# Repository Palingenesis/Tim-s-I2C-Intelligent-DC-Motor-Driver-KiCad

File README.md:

# Tim-s-I2C-Intelligent-DC-Motor-Driver-KiCad<br>
<br>
This is my Intelligent I2C DC Motor Driver<br>
It is an STM8S103F3P6 cofigured as an I2C Slave to control a DC Motor using a H Bridge.<br>
It can recives signals from Quadratic Encoder to determin direction and position.<br>
Also with a Quadratic Encoder attached you can set soft limits.<br>
There are pinouts to add hard stops<br>
There is a pinout to add a Station to set a known position<br>
Details: https://www.hackster.io/Tim_Palingenesis/tim-s-i2c-intelligent-dc-motor-driver-82cda1

<picture>
  
</picture>

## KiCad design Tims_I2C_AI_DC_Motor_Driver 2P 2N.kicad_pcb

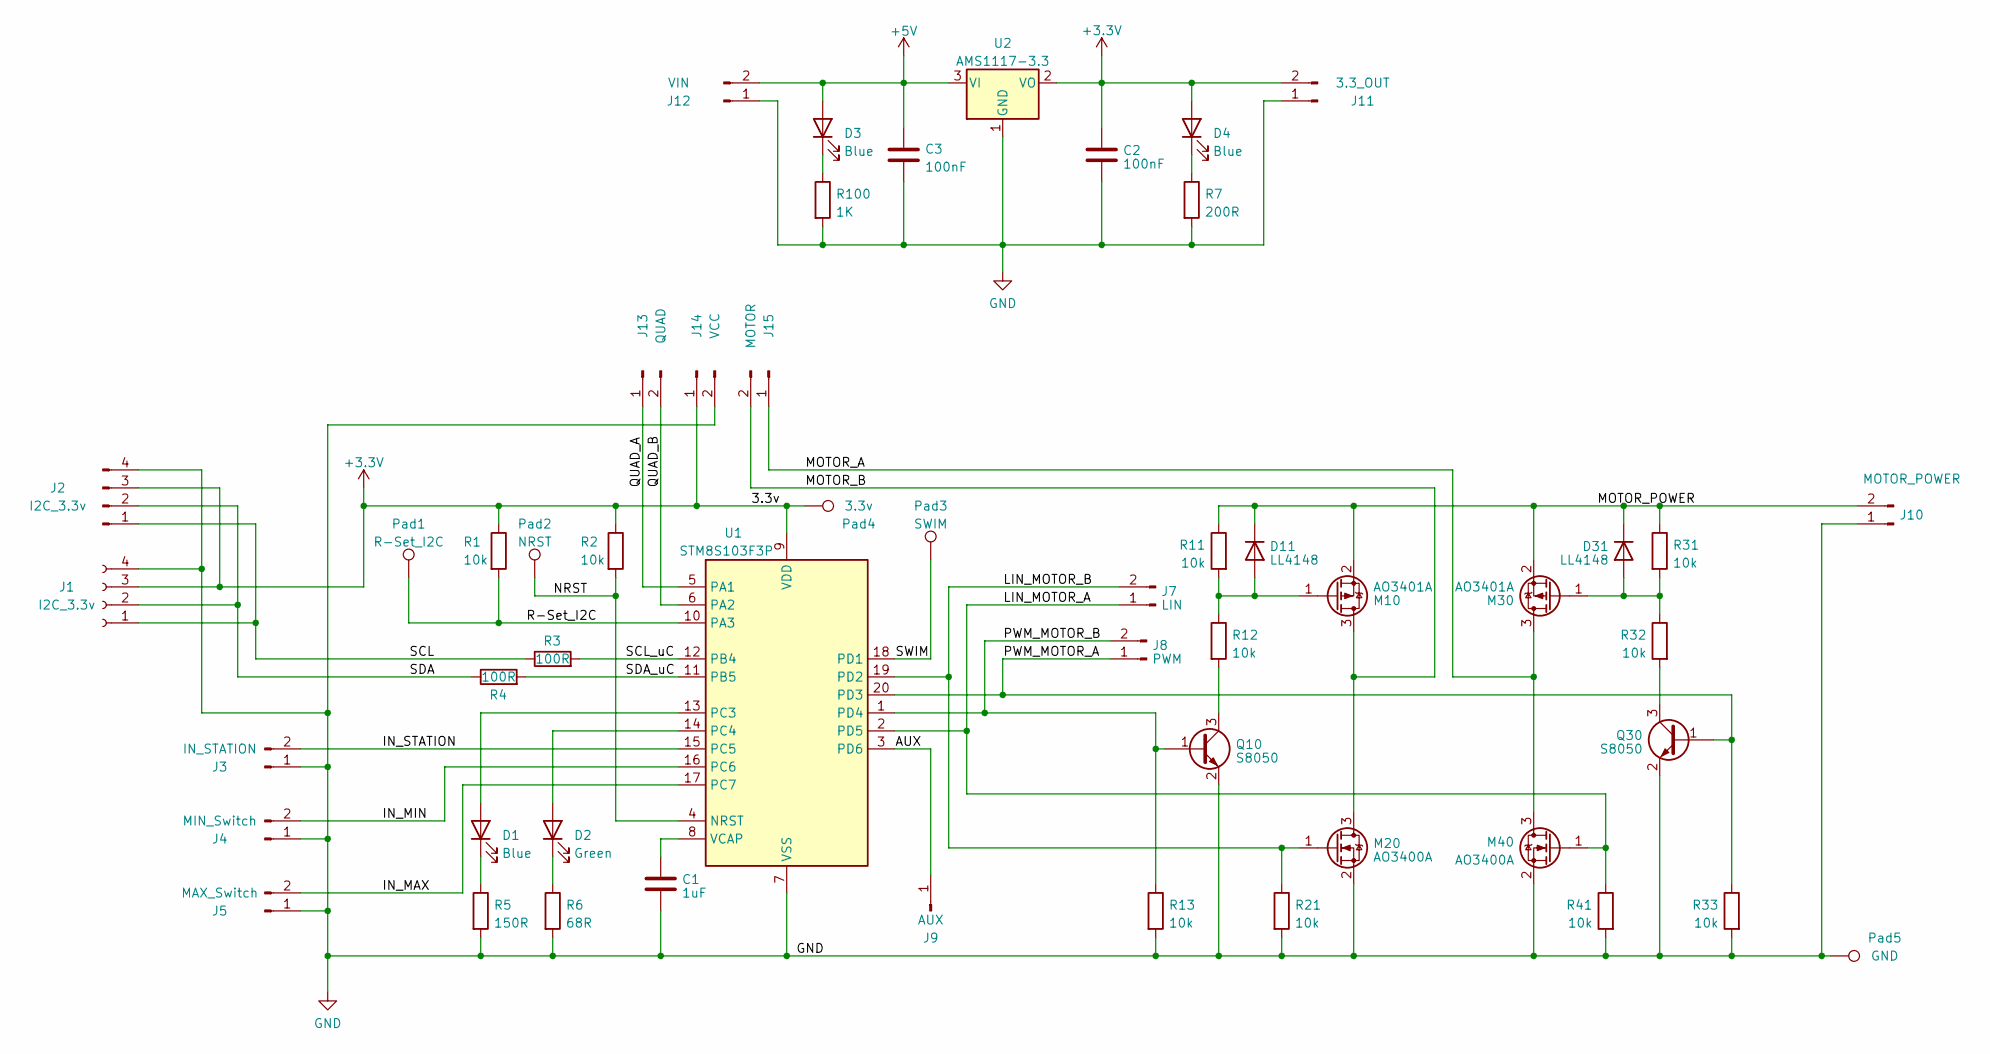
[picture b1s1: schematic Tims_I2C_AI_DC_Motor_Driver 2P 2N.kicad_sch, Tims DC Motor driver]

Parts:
C1: 1uF; C_0805_2012Metric
C2, C3: 100nF; C_0805_2012Metric
D1, D3, D4: Blue; LED_0805_2012Metric
D2: Green; LED_0805_2012Metric
D11, D31: LL4148; D_MiniMELF
J1: I2C_3.3v; PinSocket_1x04_P2.54mm_Horizontal
J2: I2C_3.3v; PinHeader_1x04_P2.54mm_Horizontal
J3: IN_STATION; PinHeader_1x02_P2.54mm_Vertical
J4: MIN_Switch; PinHeader_1x02_P2.54mm_Vertical
J5: MAX_Switch; PinHeader_1x02_P2.54mm_Vertical
J7: LIN; PinHeader_1x02_P2.54mm_Vertical
J8: PWM; PinHeader_1x02_P2.54mm_Vertical
J9: AUX; PinHeader_1x01_P2.54mm_Vertical
J10: MOTOR_POWER; PinHeader_1x02_P2.54mm_Vertical
J11: 3.3_OUT; PinHeader_1x02_P2.54mm_Vertical
J12: VIN; PinHeader_1x02_P2.54mm_Vertical
J13: QUAD; PinHeader_1x02_P2.54mm_Vertical
J14: VCC; PinHeader_1x02_P2.54mm_Vertical
J15: MOTOR; PinHeader_1x02_P2.54mm_Vertical
M10, M30: AO3401A; SOT-23
M20, M40: AO3400A; SOT-23
Pad1: R-Set_I2C; TestPoint_Pad_D1.0mm
Pad2: NRST; TestPoint_Pad_D1.0mm
Pad3: SWIM; TestPoint_Pad_D1.0mm
Pad4: 3.3v; TestPoint_Pad_D1.0mm
Pad5: GND; TestPoint_Pad_D1.0mm
Q10, Q30: S8050; SOT-23
R1, R2, R11, R12, R13, R21, R31, R32, R33, R41: 10k; R_0805_2012Metric
R3, R4: 100R; R_0805_2012Metric
R5: 150R; R_0805_2012Metric
R6: 68R; R_0805_2012Metric
R7: 200R; R_0805_2012Metric
R100: 1K; R_0805_2012Metric
U1: STM8S103F3P; TSSOP-20_4.4x6.5mm_P0.65mm
U2: AMS1117-3.3; SOT-223-3_TabPin2

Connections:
+3V3: C2.1, D4.2 (A), J1.3, J2.3, J11.2, J14.1, Pad4.1, R1.1, R2.1, U1.9 (VDD), U2.2 (VO)
+5V: C3.1, D3.2 (A), J12.2, U2.3 (VI)
/AUX: J9.1, U1.3 (PD6)
/IN_MAX: J5.2, U1.17 (PC7)
/IN_MIN: J4.2, U1.16 (PC6)
/IN_STATION: J3.2, U1.15 (PC5)
/LIN_MOTOR_A: J7.1, M40.1 (G), R41.1, U1.2 (PD5)
/LIN_MOTOR_B: J7.2, M20.1 (G), R21.1, U1.19 (PD2)
/MOTOR_A: J15.1, M30.3 (D), M40.3 (D)
/MOTOR_B: J15.2, M10.3 (D), M20.3 (D)
/MOTOR_POWER: D11.1 (K), D31.1 (K), J10.2, M10.2 (S), M30.2 (S), R11.1, R31.1
/NRST: Pad2.1, R2.2, U1.4 (NRST)
/PWM_MOTOR_A: J8.1, Q30.1 (B), R33.1, U1.20 (PD3)
/PWM_MOTOR_B: J8.2, Q10.1 (B), R13.1, U1.1 (PD4)
/QUAD_A: J13.1, U1.5 (PA1)
/QUAD_B: J13.2, U1.6 (PA2)
/R-Set_I2C: Pad1.1, R1.2, U1.10 (PA3)
/SCL: J1.1, J2.1, R3.1
/SCL_uC: R3.2, U1.12 (PB4)
/SDA: J1.2, J2.2, R4.1
/SDA_uC: R4.2, U1.11 (PB5)
/SWIM: Pad3.1, U1.18 (PD1)
GND: C1.2, C2.2, C3.2, J1.4, J2.4, J3.1, J4.1, J5.1, J10.1, J11.1, J12.1, J14.2, M20.2 (S), M40.2 (S), Pad5.1, Q10.2 (E), Q30.2 (E), R5.2, R6.2, R7.2, R13.2, R21.2, R33.2, R41.2, R100.2, U1.7 (VSS), U2.1 (GND)
unnamed: D1.2 (A), U1.13 (PC3)
unnamed: D1.1 (K), R5.1
unnamed: D2.2 (A), U1.14 (PC4)
unnamed: D2.1 (K), R6.1
unnamed: D3.1 (K), R100.1
unnamed: D4.1 (K), R7.1
unnamed: D11.2 (A), M10.1 (G), R11.2, R12.1
unnamed: D31.2 (A), M30.1 (G), R31.2, R32.1
unnamed: Q10.3 (C), R12.2
unnamed: Q30.3 (C), R32.2
unnamed: C1.1, U1.8 (VCAP)

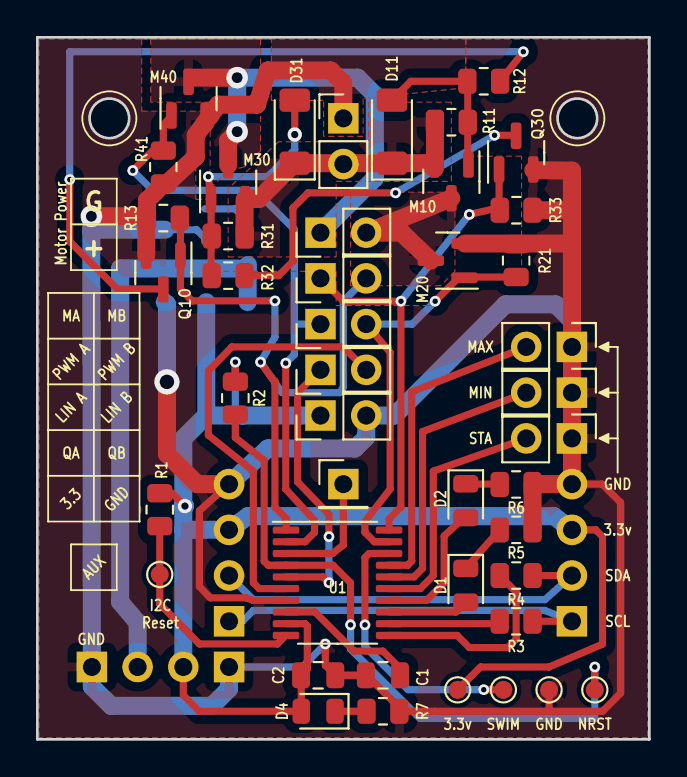
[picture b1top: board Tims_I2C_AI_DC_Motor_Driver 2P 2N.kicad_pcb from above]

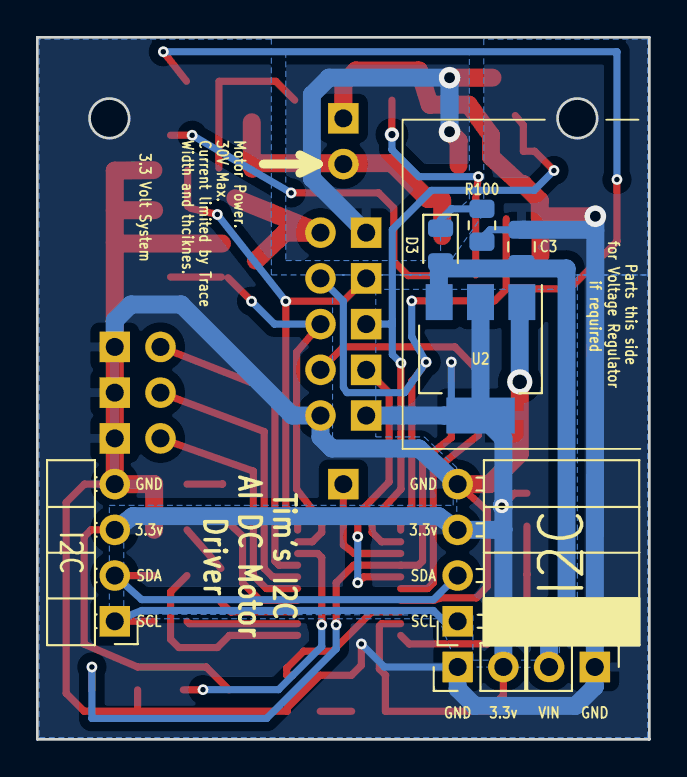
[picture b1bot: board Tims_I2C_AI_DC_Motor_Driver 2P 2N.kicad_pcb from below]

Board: 2 copper layers, 34.0 x 39.0 mm, 52 parts (8 on the bottom side), 34 nets.

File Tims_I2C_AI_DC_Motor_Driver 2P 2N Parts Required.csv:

"Id;""Designator"";""Footprint"";""Quantity"";""Designation"";""Supplier and ref"";",,,,,,,,,
"1;""M40","M20"";""SOT-23"";2;""AO3400A"";;;",,,,,,,,
"2;""J13"";""PinHeader_1x02_P2.54mm_Vertical"";1;""QUAD"";;;",,,,,,,,,
"3;""J15"";""PinHeader_1x02_P2.54mm_Vertical"";1;""MOTOR"";;;",,,,,,,,,
"4;""J4"";""PinHeader_1x02_P2.54mm_Vertical"";1;""MIN_Switch"";;;",,,,,,,,,
"5;""R21",R2,R12,R11,R32,R41,R33,R31,R1,"R13"";""R_0805_2012Metric"";10;""10k"";;;"
"6;""J5"";""PinHeader_1x02_P2.54mm_Vertical"";1;""MAX_Switch"";;;",,,,,,,,,
"7;""Q30","Q10"";""SOT-23"";2;""S8050"";;;",,,,,,,,
"8;""J14"";""PinHeader_1x02_P2.54mm_Vertical"";1;""VCC"";;;",,,,,,,,,
"9;""U1"";""TSSOP-20_4.4x6.5mm_P0.65mm"";1;""STM8S103F3P"";;;",,,,,,,,,
"10;""Pad1"";""TestPoint_Pad_D1.0mm"";1;""R-Set_I2C"";;;",,,,,,,,,
"11;""R5"";""R_0805_2012Metric"";1;""150R"";;;",,,,,,,,,
"12;""R4","R3"";""R_0805_2012Metric"";2;""100R"";;;",,,,,,,,
"13;""C1"";""C_0805_2012Metric"";1;""1uF"";;;",,,,,,,,,
"14;""M30","M10"";""SOT-23"";2;""AO3401A"";;;",,,,,,,,
"15;""D4","D1"";""LED_0805_2012Metric"";3;""Blue"";;;",,,,,,,,
"16;""R6"";""R_0805_2012Metric"";1;""68R"";;;",,,,,,,,,
"17;""J9"";""PinHeader_1x01_P2.54mm_Vertical"";1;""AUX"";;;",,,,,,,,,
"18;""R7"";""R_0805_2012Metric"";1;""200R"";;;",,,,,,,,,
"19;""Pad5"";""TestPoint_Pad_D1.0mm"";1;""GND"";;;",,,,,,,,,
"20;""Pad4"";""TestPoint_Pad_D1.0mm"";1;""3.3v"";;;",,,,,,,,,
"21;""D11","D31"";""D_MiniMELF"";2;""LL4148"";;;",,,,,,,,
"22;""J10"";""PinHeader_1x02_P2.54mm_Vertical"";1;""MOTOR_POWER"";;;",,,,,,,,,
"23;""D2"";""LED_0805_2012Metric"";1;""Green"";;;",,,,,,,,,
"24;""C2"";""C_0805_2012Metric"";2;""100nF"";;;",,,,,,,,,
"25;""Pad3"";""TestPoint_Pad_D1.0mm"";1;""SWIM"";;;",,,,,,,,,
"26;""Pad2"";""TestPoint_Pad_D1.0mm"";1;""NRST"";;;",,,,,,,,,
"27;""J3"";""PinHeader_1x02_P2.54mm_Vertical"";1;""IN_STATION"";;;",,,,,,,,,
"28;""J2"";""PinHeader_1x04_P2.54mm_Horizontal"";1;""I2C_3.3v"";;;",,,,,,,,,
"29;""J1"";""PinSocket_1x04_P2.54mm_Horizontal"";1;""I2C_3.3v"";;;",,,,,,,,,
"30;""J11"";""PinHeader_1x02_P2.54mm_Vertical"";1;""3.3_OUT"";;;",,,,,,,,,
"31;""J12"";""PinHeader_1x02_P2.54mm_Vertical"";1;""VIN"";;;",,,,,,,,,

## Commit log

2023-05-10 Add .gitattributes, .gitignore, and LICENSE.txt.
2023-05-10 Add project files.
2023-05-10 Create README.md
    added
2023-05-10 Create Info.txt
    added
2023-05-10 Update README.md
    image
2023-05-10 Update README.md
    image link
2023-05-12 Update BOM
2023-05-15 Update parts list
2023-05-15 Change BOM
